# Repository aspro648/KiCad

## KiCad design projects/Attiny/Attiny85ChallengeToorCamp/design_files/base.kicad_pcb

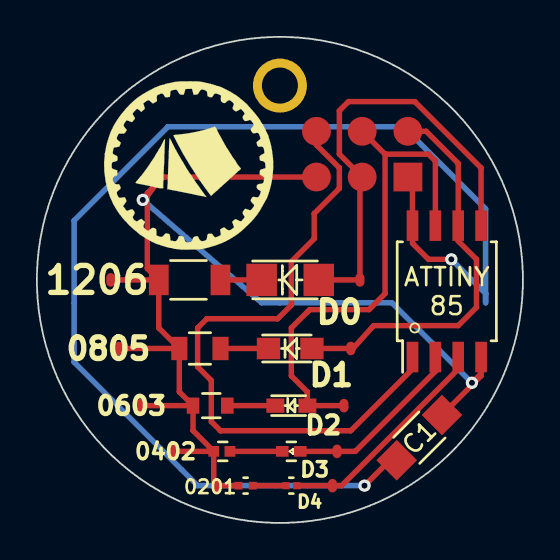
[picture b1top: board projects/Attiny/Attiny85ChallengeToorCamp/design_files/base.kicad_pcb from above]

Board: 2 copper layers, 27.0 x 27.0 mm, 25 parts (1 on the bottom side), 13 nets.

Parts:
BT1: Battery; BATT_CR2032_SMD
C1: 0.1 uF; C_1206_HandSoldering
CON1: AVR-ISP-6
D0: LED; LED-1206
D1: LED; LED-0805
D2: LED; LED-0603
D3: LED; LED_0402
D4: LED; LED_0201
IC1: IC1; SOIJ-8_5.3x5.3mm_Pitch1.27mm
P0, P1, P2, P3, P4: CONN_01X01; testPad
P5: CONN_01X01; Pin_Header_Straight_1x01
PG0, PG1, PG2, PG3, PG4: CONN_01X01; testPad
R0: 330; R_1206
R1: 330; R_0805
R2: 330; R_0603
R3: 330; R_0402
R4: 330; R_0201

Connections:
+BATT: BT1.1, C1.2, CON1.2, IC1.8
GND: BT1.2, C1.1, CON1.6, IC1.4, PG0.1, PG1.1, PG2.1, PG3.1, PG4.1, R0.2, R1.2, R2.2, R3.2, R4.2
unnamed: CON1.1, D1.2, IC1.6, P1.1
unnamed: CON1.3, D2.2, IC1.7, P2.1
unnamed: CON1.4, D0.2, IC1.5, P0.1
unnamed: CON1.5, IC1.1
unnamed: D0.1, R0.1
unnamed: D1.1, R1.1
unnamed: D2.1, R2.1
unnamed: D3.1, R3.1
unnamed: D3.2, IC1.2, P3.1
unnamed: D4.1, R4.1
unnamed: D4.2, IC1.3, P4.1

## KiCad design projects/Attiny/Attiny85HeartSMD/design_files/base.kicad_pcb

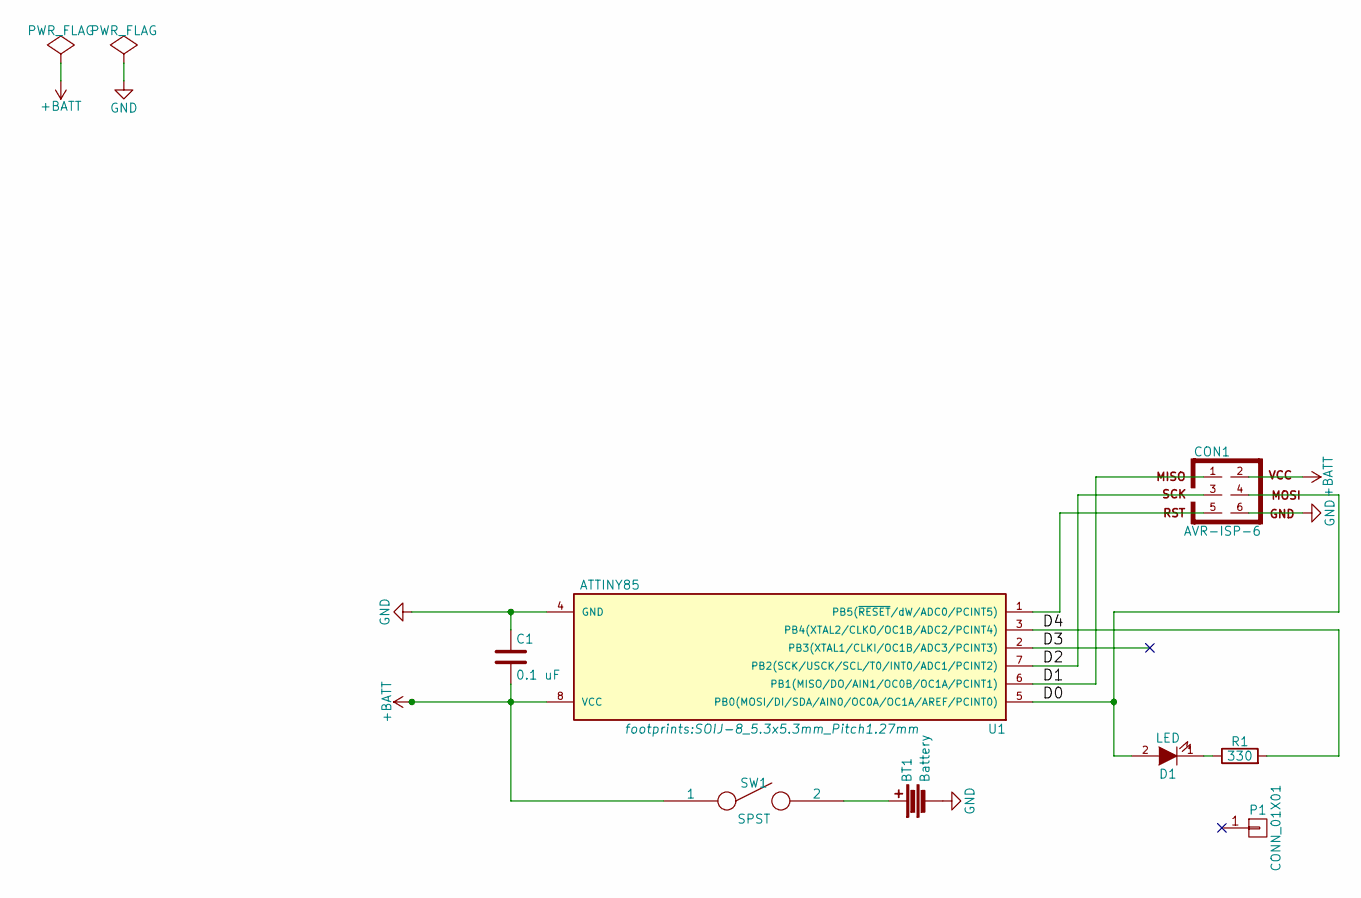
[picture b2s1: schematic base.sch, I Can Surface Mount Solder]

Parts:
BT1: Battery; BATT_CR2032_SMD
C1: 0.1 uF; C_1206_HandSoldering
CON1: AVR-ISP-6
D1: LED; LED-1206
P1: CONN_01X01; Pin_Header_Straight_1x01
R1: 330; R_1206_HandSoldering
SW1: SPST; SPST_SMD
U1: ATTINY85; SOIJ-8_5.3x5.3mm_Pitch1.27mm

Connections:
+BATT: C1.2, CON1.2, SW1.1, U1.8 (VCC)
/D0: CON1.4, D1.2 (A), U1.5 (PB0(MOSI/DI/SDA/AIN0/OC0A/OC1A/AREF/PCI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)
/D1: CON1.1, U1.6 (PB1(MISO/DO/AIN1/OC0B/OC1A/PCINT1))
/D2: CON1.3, U1.7 (PB2(SCK/USCK/SCL/T0/INT0/ADC1/PCINT2))
/D3: U1.2 (PB3(XTAL1/CLKI/OC1B/ADC3/PCINT3))
/D4: R1.2, U1.3 (PB4(XTAL2/CLKO/OC1B/ADC2/PCINT4))
GND: BT1.2, C1.1, CON1.6, U1.4 (GND)
unnamed: BT1.1, SW1.2
unnamed: CON1.5, U1.1 (PB5(~RESET~/dW/ADC0/PCINT5))
unnamed: D1.1 (K), R1.1

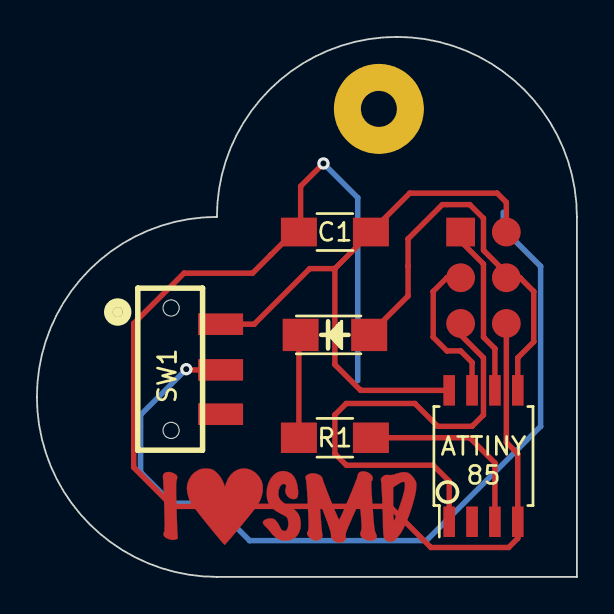
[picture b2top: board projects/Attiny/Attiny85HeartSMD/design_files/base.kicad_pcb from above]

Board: 2 copper layers, 30.0 x 30.0 mm, 8 parts (1 on the bottom side), 9 nets.

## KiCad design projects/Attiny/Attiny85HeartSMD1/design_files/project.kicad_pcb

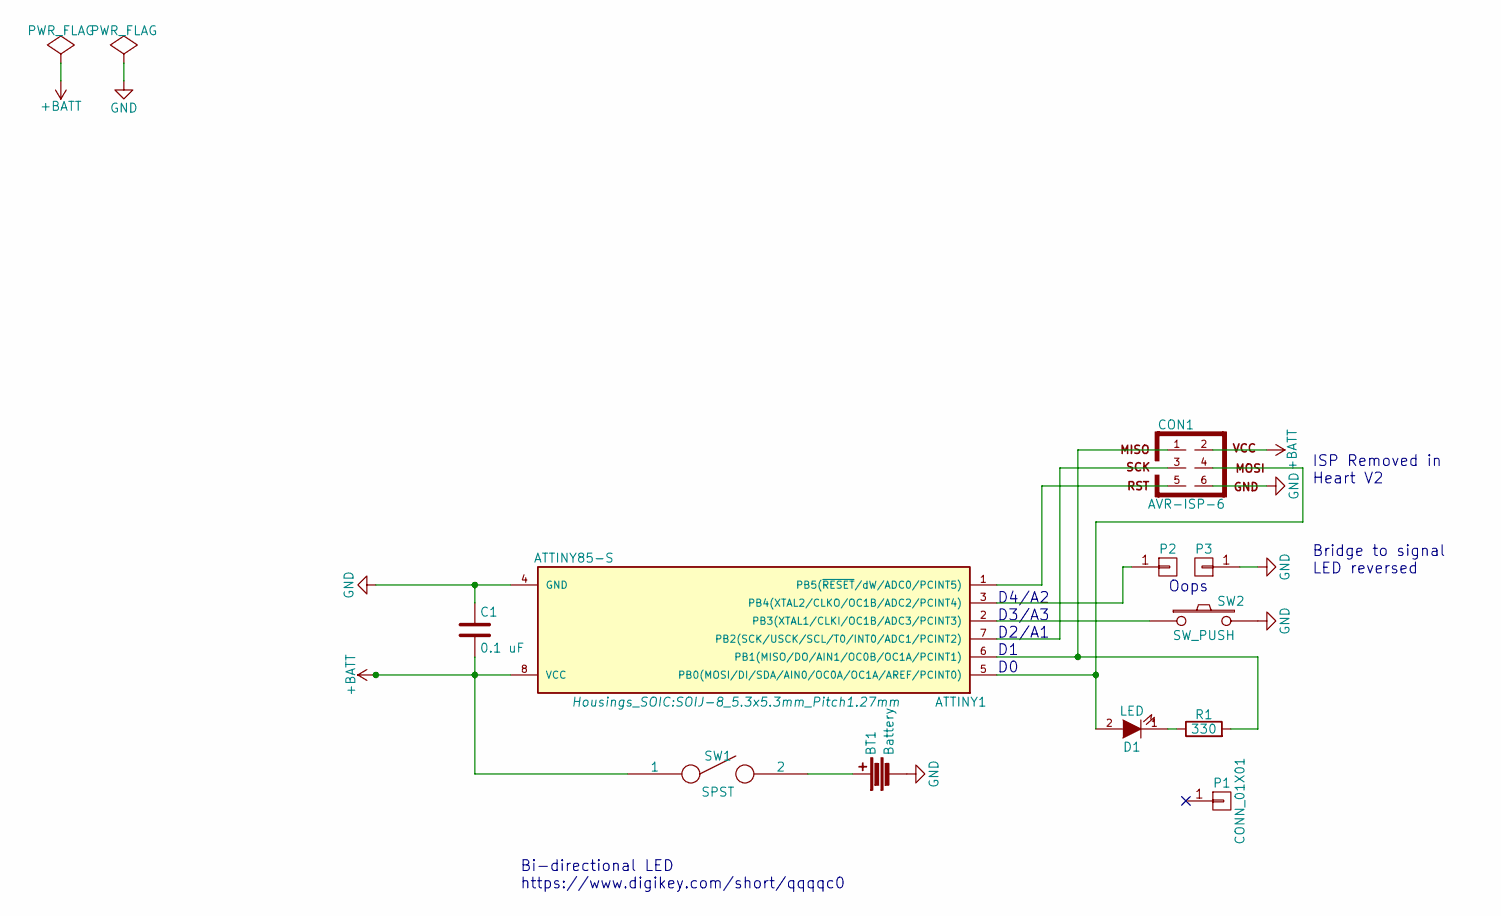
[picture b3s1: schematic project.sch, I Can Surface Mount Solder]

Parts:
ATTINY1: ATTINY85-S; SOIJ-8_5.3x5.3mm_Pitch1.27mm
BT1: Battery; BATT_CR2032_SMD
C1: 0.1 uF; C_1206_HandSoldering
CON1: AVR-ISP-6
D1: LED; LED-1206
P1: CONN_01X01; Pin_Header_Angled_1x01
P2, P3: CONN_01X01; Pin_Header_Straight_1x01
R1: 330; Resistor_SMDuniversal_0805to1206_HandSoldering
SW1: SPST; SPST_SMD
SW2: SW_PUSH; SW_SMD_PUSH

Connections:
+BATT: ATTINY1.8 (VCC), C1.2, CON1.2, SW1.1
GND: ATTINY1.4 (GND), BT1.2, C1.1, CON1.6, P3.1, SW2.2
unnamed: ATTINY1.1 (PB5(~RESET~/dW/ADC0/PCINT5)), CON1.5
unnamed: ATTINY1.2 (PB3(XTAL1/CLKI/OC1B/ADC3/PCINT3)), SW2.1
unnamed: ATTINY1.3 (PB4(XTAL2/CLKO/OC1B/ADC2/PCINT4)), P2.1
unnamed: ATTINY1.5 (PB0(MOSI/DI/SDA/AIN0/OC0A/OC1A/AREF/PCI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), CON1.4, D1.2 (A)
unnamed: ATTINY1.6 (PB1(MISO/DO/AIN1/OC0B/OC1A/PCINT1)), CON1.1, R1.2
unnamed: ATTINY1.7 (PB2(SCK/USCK/SCL/T0/INT0/ADC1/PCINT2)), CON1.3
unnamed: BT1.1, SW1.2
unnamed: D1.1 (K), R1.1

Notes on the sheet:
Bi-directional LED https://www.digikey.com/short/qqqqc0
Oops
Bridge to signal LED reversed
D4/A2 D3/A3 D2/A1 D1 D0
ISP Removed in Heart V2

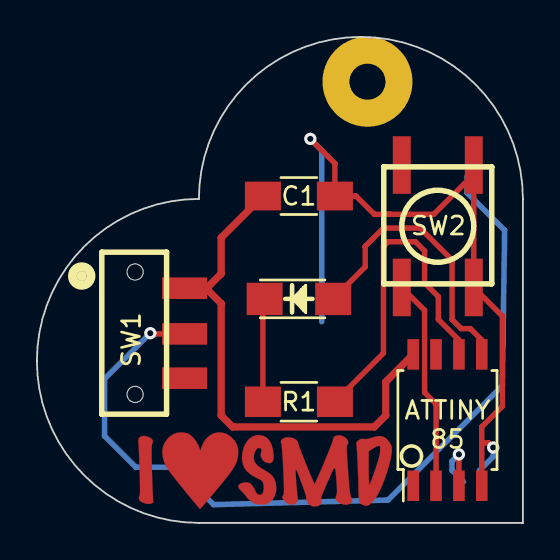
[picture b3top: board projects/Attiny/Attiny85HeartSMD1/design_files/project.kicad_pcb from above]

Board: 2 copper layers, 27.0 x 27.0 mm, 10 parts (1 on the bottom side), 8 nets.

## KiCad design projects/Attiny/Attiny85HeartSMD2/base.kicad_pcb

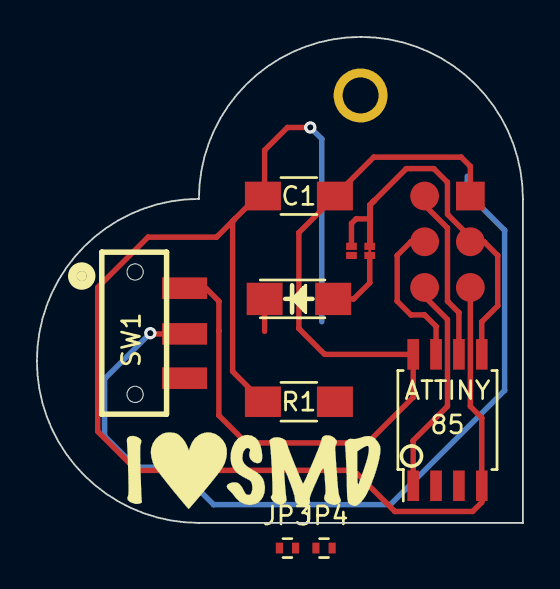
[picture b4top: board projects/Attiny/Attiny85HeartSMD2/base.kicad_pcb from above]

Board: 2 copper layers, 27.0 x 27.0 mm, 12 parts (1 on the bottom side), 10 nets.

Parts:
ATTINY: ATTINY; SOIJ-8_5.3x5.3mm_Pitch1.27mm
BT1: Battery; BATT_CR2032_SMD
C1: 0.1 uF; C_1206_HandSoldering
CON1: AVR-ISP-6
D1: LED; LED-1206
JP1, JP4: Jumper_NO_Small; R_0402
JP2, JP3: Jumper_NC_Small; R_0402
P1: CONN_01X01; Pin_Header_Straight_1x01
R1: 330; R_1206_HandSoldering
SW1: SW_PUSH; SPST_SMD

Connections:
+BATT: ATTINY.8, C1.2, CON1.2
GND: ATTINY.4, BT1.2, C1.1, CON1.6, R1.2, SW1.2
unnamed: ATTINY.6, CON1.1
unnamed: ATTINY.7, CON1.3
unnamed: ATTINY.5, CON1.4, JP1.1, JP2.1
unnamed: ATTINY.1, CON1.5
unnamed: D1.1, JP1.2, JP3.1
unnamed: D1.2, JP4.1
unnamed: ATTINY.2, SW1.1
unnamed: JP4.2, R1.1

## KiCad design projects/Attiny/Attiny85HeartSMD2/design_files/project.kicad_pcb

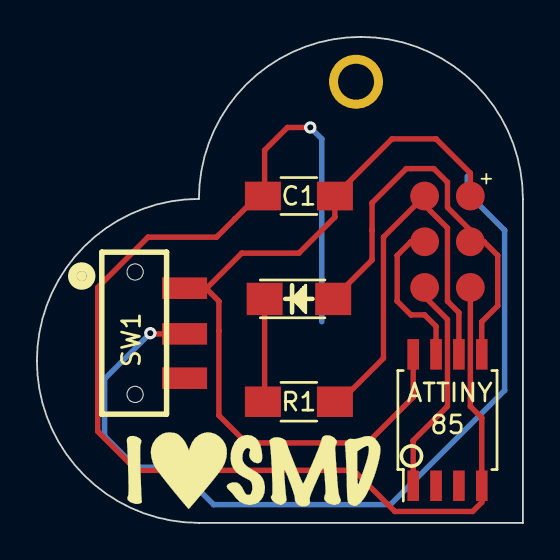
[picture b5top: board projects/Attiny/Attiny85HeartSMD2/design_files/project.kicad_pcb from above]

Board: 2 copper layers, 27.0 x 27.0 mm, 8 parts (1 on the bottom side), 8 nets.

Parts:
BT1: Battery; BATT_CR2032_SMD
C1: 0.1 uF; C_1206_HandSoldering
CON1: AVR-ISP-6
D1: LED; LED-1206
IC1: ATTINY; SOIJ-8_5.3x5.3mm_Pitch1.27mm
P1: CONN_01X01; Pin_Header_Straight_1x01
R1: 330; R_1206_HandSoldering
SW1: SPST; SPST_SMD

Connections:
+BATT: C1.2, CON1.2, IC1.8, SW1.1
GND: BT1.2, C1.1, CON1.6, IC1.4
unnamed: BT1.1, SW1.2
unnamed: CON1.1, IC1.6, R1.2
unnamed: CON1.3, IC1.7
unnamed: CON1.4, D1.2, IC1.5
unnamed: CON1.5, IC1.1
unnamed: D1.1, R1.1

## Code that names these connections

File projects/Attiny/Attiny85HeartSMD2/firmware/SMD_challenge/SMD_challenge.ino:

/*
This sketch works with either the SMD Challenge:
https://hackaday.io/project/25265-an-unfortunate-smd-project
or the I Can Surface Mount Solder Project:
https://www.instructables.com/id/I-Can-Surface-Mount-Solder/


License
=======
[Attribution-ShareAlike 3.0 United States (CC BY-SA 3.0 US)](https://creativecommons.org/licenses/by-sa/3.0/us/)

You are free to:

- Share — copy and redistribute the material in any medium or format
- Adapt — remix, transform, and build upon the material

Under the following terms:

- Attribution — You must give appropriate credit, provide a link to the license, and indicate if changes were made. You may do so in any reasonable manner, but not in any way that suggests the licensor endorses you or your use.
- ShareAlike — If you remix, transform, or build upon the material, you must distribute your contributions under the same license as the original.


Heartbeat code based on Emily Lovell's LilyTiny:
http://dlnmh9ip6v2uc.cloudfront.net/datasheets/E-Textiles/Lilypad/LilyTiny.ino
https://users.soe.ucsc.edu/~emme/

Arduino pinout development based on FunShield:
https://www.tindie.com/products/MakersBox/funshield-arduino-shield-kit/

Not all Attiny cores support the tone() function. Try this one
https://github.com/SpenceKonde/ATTinyCore

ATMEL ATTINY45/85 Pin Assignments
                   +-\/-+
  Ain0 (D 5) PB5  1|    |8  Vcc
  Ain3 (D 3) PB3  2|    |7  PB2 (D 2) Ain1
  Ain2 (D 4) PB4  3|    |6  PB1 (D 1) pwm1
             GND  4|    |5  PB0 (D 0) pwm0

*/


int LEDS[] = {1, 2, 3, 4};
bool STATES[] = {true, true, true, true, true};


// Pins are different between Arduino and Attiny
#if defined(__AVR_ATtiny85__)
  #define ARDUINO 0
  #define ledPin 0     
  #define lightPin 3    // CdS or pushbutton hooked from PB4 (Pin 3, A2/D4) to ground
  #define lightPullUp 3
  #define touchPin 1
  #define touchPullUp 2
#else  
  #define ARDUINO 1
  #define ledPin 9  // RGB red
  #define lightPin A1
  #define lightPullUp A1
  #define touchPin A3
  #define touchPullUp A3
#endif


int on_time = 10;  // in seconds


void setup(){
  #if (ARDUINO)
    Serial.begin(9600);
    Serial.println("SMD_heart");
  #endif

  // setup heart pin
  pinMode(ledPin, INPUT);

  // setup other LEDs
  for(int LED=0; LED<(sizeof(LEDS)/sizeof(int)); LED++){
    pinMode(LEDS[LED], OUTPUT);
    digitalWrite(LEDS[LED], STATES[LED]);
  }
}


void loop(){
  heartBeat(on_time);
}


boolean heartBeat(int on_time){
  // based on http://dlnmh9ip6v2uc.cloudfront.net/datasheets/E-Textiles/Lilypad/LilyTiny.ino

  // Variables and constants for fading pin. Needs to be a hardware PWM pin; on
  byte heartStage = 0;
  int heartBrightness = 0;
  byte heartCounter = 0;
  long off_time = millis() + on_time * 1000;
  pinMode(ledPin, OUTPUT);
  digitalWrite(ledPin, HIGH);

  while(millis() < off_time){
    delayMicroseconds(9999);
    // calculate brightness for heartbeat pin (by cycling 
    // through phases of pulse pattern)
    heartCounter++;
    if (heartCounter > 144) {
      heartStage = (heartStage + 1) % 4;
      heartCounter = 0;
    }
    else {
      switch(heartStage) {
        case 0:
          analogWrite(ledPin, heartBrightness);
          heartCounter += 144/12.0;
          heartBrightness += 255/12.0;
          if (heartBrightness > 255)
            heartBrightness = 255;
          break;
        case 1:
          analogWrite(ledPin, heartBrightness);
          heartCounter += 144/24.0;
          heartBrightness -= 255/24.0;
          if (heartBrightness < 0)
            heartBrightness = 0;
          break;
        case 2:
          analogWrite(ledPin, heartBrightness);
          heartCounter += 144/12.0;
          heartBrightness += 255/12.0;
          if (heartBrightness > 255)
            heartBrightness = 255;
          break;
        case 3:
          analogWrite(ledPin, heartBrightness);
          heartCounter += 144/72.0;
          heartBrightness -= 255/72.0;
          if (heartBrightness < 0)
            heartBrightness = 0;
          break;
      }//switch
    }//else
    
    // blink other LEDs randomly
    for(int LED=0; LED<(sizeof(LEDS)/sizeof(int)); LED++){
      if(random(40) == 1){
        STATES[LED] = !STATES[LED];
        digitalWrite(LEDS[LED], STATES[LED]);  
      }
    }     
  }
  
  // go to a low power state
  digitalWrite(ledPin, LOW);
  pinMode(ledPin, INPUT);
  return(true);
}
